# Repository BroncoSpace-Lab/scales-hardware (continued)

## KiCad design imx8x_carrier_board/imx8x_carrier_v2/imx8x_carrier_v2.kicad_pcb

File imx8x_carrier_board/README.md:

# Design Notes

This design for the i.MX 8X SCALES Custom Devlopment Board is mostly based on PhyTec's Development Kit design. For clarity, this version of the SCALES board will be called "SCALES board" and the PhyTec Devlopment Kit board will be called "dev kit."

Version 1 of the SCALES board is for development only. Future versions of the board as we develop for flight will include the power and watchdog system on the same board as the flight computer. The development boards for each of these subsystems will be isolated for testing before combining them into one board for flight.

Most of this design is based on the dev kit schematics and Hardware Manual, available from PhyTec upon request. This link to the [dev kit](https://www.phytec.com/product/phycore-i-mx-8-development-kit/) should supply the necessary supporting documentation used for this design.

## Elements of the SCALES Board

The main elements of the dev kit that are used in the SCALES board are:

- Micro USB UART Debug port
- 2 Ethernet ports
- Micro SD Card Reader

Elements of the dev kit that will be altered significantly for the SCALES board:

- Power input and distribution
- SPI
- UART
- I2C

## Schematic Design

The schematic is organized into heirarchical pages to make the page cleaner and more concise.

The root of the schematic includes the board to board (B2B) connectors that interface the SOM to the SCALES board. The same connectors are used in the dev kit.

This page will be organized to show essential connections between blocks as the schematic progresses.

This version of the SCALES board for development will use DF11 connectors for power input, SPI, UART, and I2C. Later versions of this board for flight will use Gecko connectors. The DF11 is used to reduce lead times for the initial versions of the board.

Important note: all signals from the B2B connectors on the SCALES board begin with "X_". The same naming convention is used in the dev kit.

### Micro USB UART Debug

Replicated as much of the dev kit design as possible. Main changes are:

- MBR0520L is no longer manufactured. using MBR0520LT
- There is a dip switch and a multiplexor that allow for FTDI to be enabled. The dip switch and multiplexor were removed. (they might be brought back later as we continue to develop UART)

### Ethernet

The i.MX 8X SOM has an onboard ethernet transciever for ETH0, but not ETH1. Any carrier board connected to the SOM is required to implement a transciever for ETH1. The design for this transciever and the supporting ethernet female connector plugs were directly pulled from the dev kit schematic, with the only changes being specific part numbers for components and connectors. The functionality is the same.

### Micro SD Card Reader

Everything in the SCALES board is the same as the dev kit except:

- No part # for dip switch selected yet
- Different SD card reader part # used. The one use in the dev kit was not available from JLC PCB.
- Removed Enable_WIFI switch. This signal is pulled low elsewhere for the multiplexor to still work and we do not need WiFi on the SCALES board, so the functionality was removed.

The multiplexor and switches allow you to switch between NAND flash/boot and SD flash/boot. You cannot use SD at the same time as WiFi. Since we will not be using WiFi, this will not be an issue, but the Enable_WIFI signal still needs to be pulled low for the multiplexor to work for switching between SD and NAND.

### Power Input and Distribution

The dev kit used a 12V input. The SOM only requires a 3.3V input at 2A, so we will be using a 3.3V input for the SCALES board.

The dev kit also gets input power from a barrel jack wall plug. The SCALES board (version 1 development) will be getting input from a DF11 2x8 pin connector through a tabletop power supply.

The DF11 power connector used in the SCALES board will also be able to get input power from the SCALES Power Distribution board. Pinouts are still being discussed across boards to maintain consistency.

The power input and distribution system of the imx SCALES board is still in development. Trying to figure out how the voltage rails will translate from the dev kit without the 12V input.

The i.MX 8X SOM generates 3.3V and 1.8V voltage rails, but the dev kit does not use them. Not sure if SCALES should just use the rails or generate new rails.

The dev kit also has a 5V rail, but all the components that use the 5V rail will not be used in SCALES, so it will most likely be omitted. 

### SPI

There are expansion header pins on the last page of the dev kit schematic that allow connection to the SPI pins not in use elsewhere on the board. These signals will be connected to the DF11 for use on the SCALES board.

### UART

The UART on the i.MX 8X dev kit is accessible through header pins, RS232, and the Debug USB. We already covered the Debug USB, so figuring out how to use the signals from the header pins and the RS232 for the DF11 is the next step for the SCALES board. Still in progress.

### I2C

I2C on the dev kit seems pretty straightforward, all that needs to be done is confirm the pinouts for the DF11 with the peripheral board to make sure that everything lines up correctly across both boards for continuity in the design of the system.

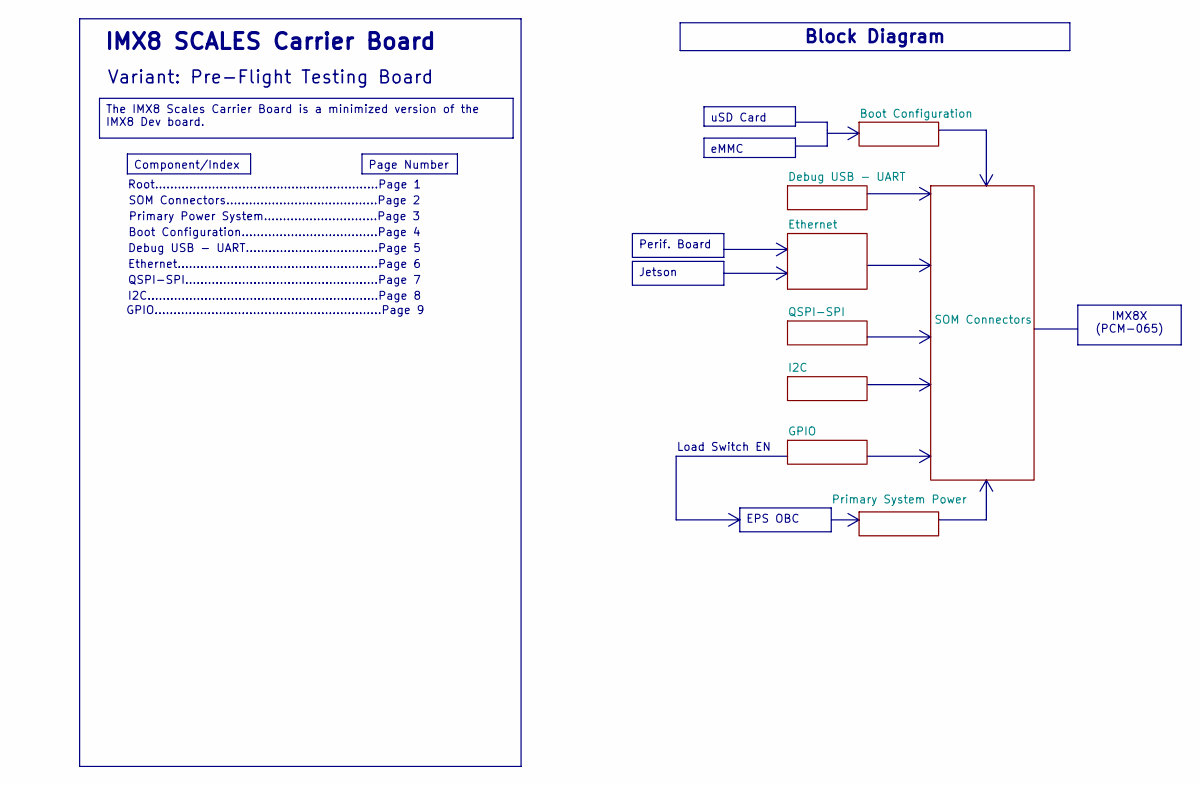
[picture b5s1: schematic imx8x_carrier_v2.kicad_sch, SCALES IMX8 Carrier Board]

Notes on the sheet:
Load Switch EN
Root...........................................................Page 1
SOM Connectors........................................Page 2
Debug USB - UART...................................Page 5
Boot Configuration....................................Page 4
Ethernet.....................................................Page 6
Primary Power System..............................Page 3
QSPI-SPI...................................................Page 7
Variant: Pre-Flight Testing Board
GPIO............................................................Page 9
IMX8 SCALES Carrier Board
I2C.............................................................Page 8
Jetson
Perif. Board
Block Diagram
Component/Index
uSD Card
The IMX8 Scales Carrier Board is a minimized version of the IMX8 Dev board.
IMX8X (PCM-065)
Page Number
EPS OBC
eMMC

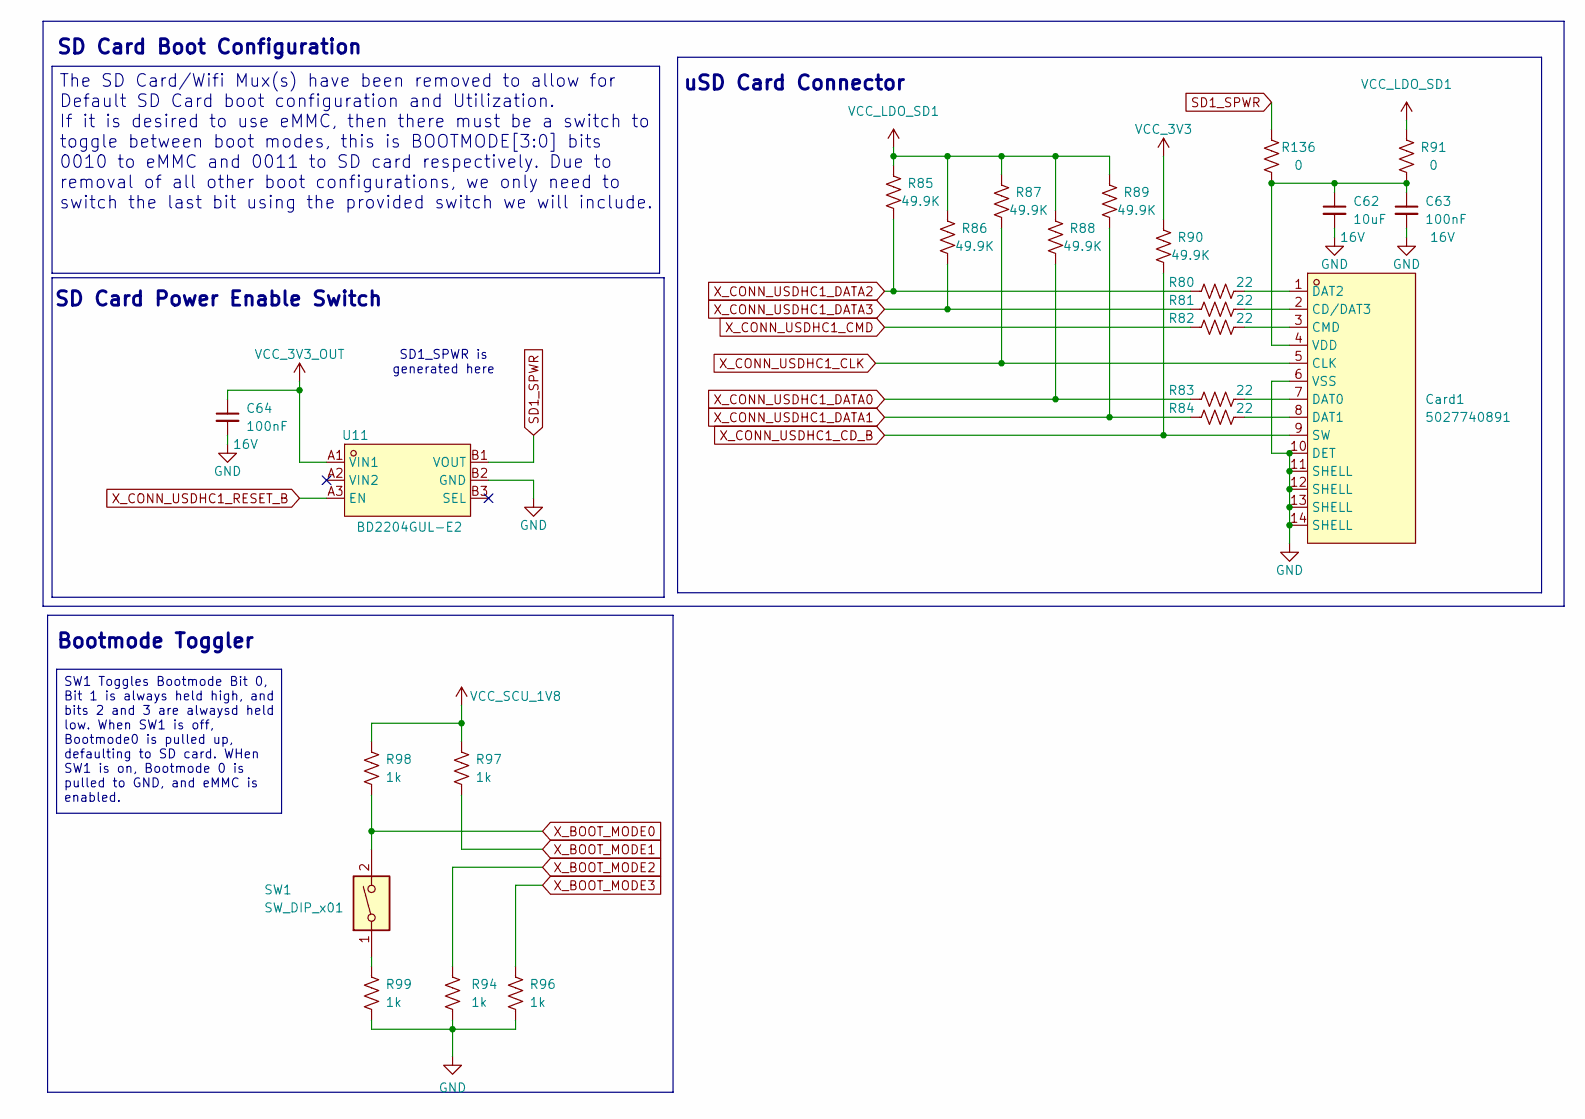
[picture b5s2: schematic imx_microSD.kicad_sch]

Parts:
C62: 10uF; Voltage 16V
C63, C64: 100nF; Voltage 16V
Card1: 5027740891; TF-SMD_5027740891; LCSC Part C330255
R80, R81, R82, R83, R84: 22
R85, R86, R87, R88, R89, R90: 49.9K
R91, R136: 0
R94, R96, R97, R98, R99: 1k
SW1: SW_DIP_x01
U11: BD2204GUL-E2; BGA-6_L1.5-W1.0-P0.50_BD2204GUL-E2; LCSC Part C314699

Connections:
GND: C62.2, C63.2, C64.2, Card1.6 (VSS), Card1.10 (DET), Card1.11 (SHELL), Card1.12 (SHELL), Card1.13 (SHELL), Card1.14 (SHELL), R94.2, R96.2, R99.2, U11.B2 (GND); also elsewhere on the board
unnamed: Card1.2 (CD/DAT3), R81.1
unnamed: Card1.3 (CMD), R82.1
unnamed: Card1.7 (DAT0), R83.1
unnamed: Card1.8 (DAT1), R84.1
unnamed: Card1.1 (DAT2), R80.1
unnamed: C62.1, C63.1, Card1.4 (VDD), R91.2, R136.2
unnamed: R99.1, SW1.1
SD1_SPWR: R136.1, U11.B1 (VOUT)
VCC_3V3: R90.1; also elsewhere on the board
VCC_3V3_OUT: C64.1, U11.A1 (VIN1); also elsewhere on the board
VCC_LDO_SD1: R85.1, R86.1, R87.1, R88.1, R89.1, R91.1; also elsewhere on the board
VCC_SCU_1V8: R97.1, R98.1; also elsewhere on the board
X_BOOT_MODE0: R98.2, SW1.2; also elsewhere on the board
X_BOOT_MODE1: R97.2; also elsewhere on the board
X_BOOT_MODE2: R94.1; also elsewhere on the board
X_BOOT_MODE3: R96.1; also elsewhere on the board
X_CONN_USDHC1_CD_B: Card1.9 (SW), R90.2; also elsewhere on the board
X_CONN_USDHC1_CLK: Card1.5 (CLK), R87.2; also elsewhere on the board
X_CONN_USDHC1_CMD: R82.2; also elsewhere on the board
X_CONN_USDHC1_DATA0: R83.2, R88.2; also elsewhere on the board
X_CONN_USDHC1_DATA1: R84.2, R89.2; also elsewhere on the board
X_CONN_USDHC1_DATA2: R80.2, R85.2; also elsewhere on the board
X_CONN_USDHC1_DATA3: R81.2, R86.2; also elsewhere on the board
X_CONN_USDHC1_RESET_B: U11.A3 (EN); also elsewhere on the board

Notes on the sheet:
SD Card Boot Configuration
SD Card Power Enable Switch
uSD Card Connector
Bootmode Toggler
SD1_SPWR is generated here
The SD Card/Wifi Mux(s) have been removed to allow for Default SD Card boot configuration and Utilization. If it is desired to use eMMC, then there must be a switch to toggle between boot modes, this is BOOTMODE[3:0] bits 0010 to eMMC and 0011 to SD card respectively. Due to removal of all other bo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
SW1 Toggles Bootmode Bit 0, Bit 1 is always held high, and bits 2 and 3 are alwaysd held low. When SW1 is off, Bootmode0 is pulled up, defaulting to SD card. WHen SW1 is on, Bootmode 0 is pulled to GND, and eMMC is enabled.

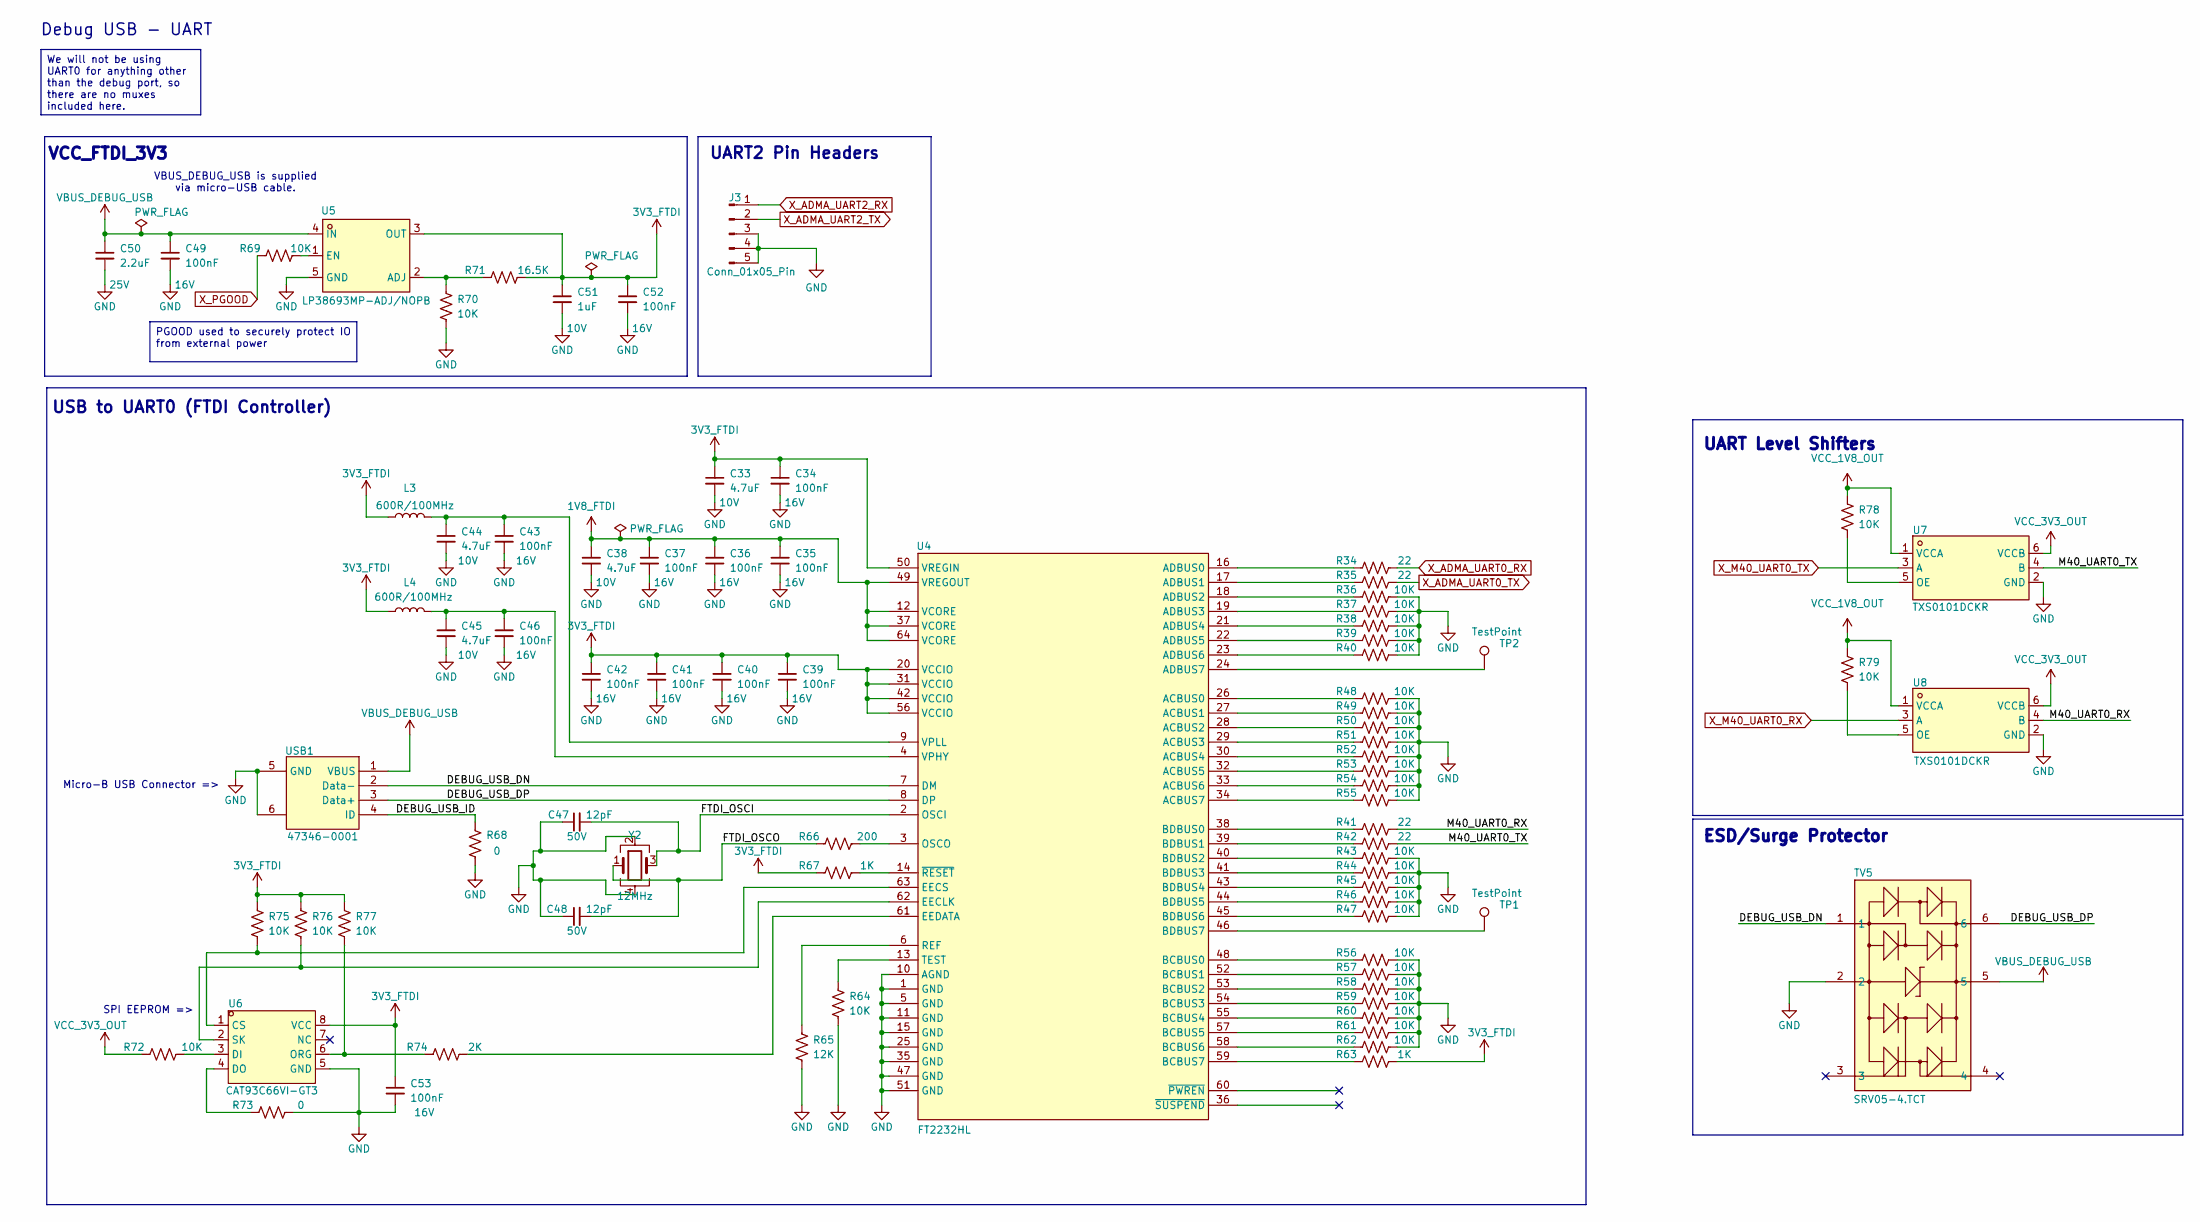
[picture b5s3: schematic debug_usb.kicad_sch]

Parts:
C33, C38, C44, C45: 4.7uF; C_0603_1608Metric; Voltage 10V
C34, C35, C36, C37, C39, C40, C41, C42, C43, C46, C49, C52, C53: 100nF; C_0603_1608Metric; Voltage 16V
C47, C48: 12pF; C_0603_1608Metric; Voltage 50V
C50: 2.2uF; C_0603_1608Metric; Voltage 25V
C51: 1uF; C_0603_1608Metric; Voltage 10V
J3: Conn_01x05_Pin; PinHeader_1x05_P2.54mm_Vertical
L3, L4: 600R/100MHz; L0805
R34, R35, R41, R42: 22; R_0402_1005Metric
R36, R37, R38, R39, R40, R43, R44, R45, R46, R47, R48, R49, R50, R51, R52, R53, R54, R55, R56, R57, R58, R59, R60, R61, R62, R64, R69, R70, R72, R75, R76, R77, R78, R79: 10K; R_0402_1005Metric
R63, R67: 1K; R_0402_1005Metric
R65: 12K; R_0402_1005Metric
R66: 200; R_0402_1005Metric
R68, R73: 0; R_0402_1005Metric
R71: 16.5K; R_0402_1005Metric
R74: 2K; R_0402_1005Metric
TP1, TP2: TestPoint; TestPoint_THTPad_1.0x1.0mm_Drill0.5mm
TV5: SRV05-4.TCT; SOT-23-6_L2.9-W1.6-P0.95-LS2.8-BR; LCSC Part C13612
U4: FT2232HL; LQFP-64_L10.0-W10.0-P0.50-LS12.0-TL; LCSC Part C27882
U5: LP38693MP-ADJ/NOPB; SOT-223-5_L6.5-W3.5-P1.50-LS7.0-BL; LCSC Part C181420
U6: CAT93C66VI-GT3; SOIC-8_L4.9-W3.9-P1.27-LS6.0-BL; LCSC Part C890471
U7, U8: TXS0101DCKR; SC-70-6_L2.0-W1.3-P0.65-LS2.1-BR; LCSC Part C132031
USB1: 47346-0001; MICRO-USB-SMD_47346-0001; LCSC Part C132560
Y2: 12MHz; CRYSTAL-SMD_4P-L3.2-W2.5-BL; LCSC Part C9002

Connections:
1V8_FTDI: C35.1, C36.1, C37.1, C38.1, U4.12 (VCORE), U4.37 (VCORE), U4.49 (VREGOUT), U4.64 (VCORE)
3V3_FTDI: C33.1, C34.1, C39.1, C40.1, C41.1, C42.1, C51.1, C52.1, C53.1, L3.1, L4.1, R63.1, R67.2, R71.1, R75.1, R76.1, R77.1, U4.20 (VCCIO), U4.31 (VCCIO), U4.42 (VCCIO), U4.50 (VREGIN), U4.56 (VCCIO), U5.3 (OUT), U6.8 (VCC)
/Debug USB - UART/DEBUG_USB_DN: TV5.1, U4.7 (DM), USB1.2 (Data-)
/Debug USB - UART/DEBUG_USB_DP: TV5.6, U4.8 (DP), USB1.3 (Data+)
/Debug USB - UART/DEBUG_USB_ID: R68.1, USB1.4 (ID)
/Debug USB - UART/FTDI_OSCI: C47.2, U4.2 (OSCI), Y2.3
/Debug USB - UART/FTDI_OSCO: C48.2, R66.2, Y2.1
/Debug USB - UART/M40_UART0_RX: R41.1, U8.4 (B)
/Debug USB - UART/M40_UART0_TX: R42.1, U7.4 (B)
GND: C33.2, C34.2, C35.2, C36.2, C37.2, C38.2, C39.2, C40.2, C41.2, C42.2, C43.2, C44.2, C45.2, C46.2, C47.1, C48.1, C49.2, C50.2, C51.2, C52.2, C53.2, J3.3, J3.4, J3.5, R36.1, R37.1, R38.1, R39.1, R40.1, R43.1, R44.1, R45.1, R46.1, R47.1, R48.1, R49.1, R50.1, R51.1, R52.1, R53.1, R54.1, R55.1, R56.1, R57.1, R58.1, R59.1, R60.1, R61.1, R62.1, R64.2, R65.2, R68.2, R70.2, R73.1, TV5.2, U4.1 (GND), U4.5 (GND), U4.10 (AGND), U4.11 (GND), U4.15 (GND), U4.25 (GND), U4.35 (GND), U4.47 (GND), U4.51 (GND), U5.5 (GND), U6.5 (GND), U7.2 (GND), U8.2 (GND), USB1.5 (GND), USB1.6, Y2.2, Y2.4; also elsewhere on the board
unnamed: R48.2, U4.26 (ACBUS0)
unnamed: R49.2, U4.27 (ACBUS1)
unnamed: R50.2, U4.28 (ACBUS2)
unnamed: R51.2, U4.29 (ACBUS3)
unnamed: R52.2, U4.30 (ACBUS4)
unnamed: R53.2, U4.32 (ACBUS5)
unnamed: R54.2, U4.33 (ACBUS6)
unnamed: R55.2, U4.34 (ACBUS7)
unnamed: R34.2, U4.16 (ADBUS0)
unnamed: R35.2, U4.17 (ADBUS1)
unnamed: R36.2, U4.18 (ADBUS2)
unnamed: R37.2, U4.19 (ADBUS3)
unnamed: R38.2, U4.21 (ADBUS4)
unnamed: R39.2, U4.22 (ADBUS5)
unnamed: R40.2, U4.23 (ADBUS6)
unnamed: TP2.1, U4.24 (ADBUS7)
unnamed: R56.2, U4.48 (BCBUS0)
unnamed: R57.2, U4.52 (BCBUS1)
unnamed: R58.2, U4.53 (BCBUS2)
unnamed: R59.2, U4.54 (BCBUS3)
unnamed: R60.2, U4.55 (BCBUS4)
unnamed: R61.2, U4.57 (BCBUS5)
unnamed: R62.2, U4.58 (BCBUS6)
unnamed: R63.2, U4.59 (BCBUS7)
unnamed: R41.2, U4.38 (BDBUS0)
unnamed: R42.2, U4.39 (BDBUS1)
unnamed: R43.2, U4.40 (BDBUS2)
unnamed: R44.2, U4.41 (BDBUS3)
unnamed: R45.2, U4.43 (BDBUS4)
unnamed: R46.2, U4.44 (BDBUS5)
unnamed: R47.2, U4.45 (BDBUS6)
unnamed: TP1.1, U4.46 (BDBUS7)
unnamed: R76.2, U4.62 (EECLK), U6.2 (SK)
unnamed: R75.2, U4.63 (EECS), U6.1 (CS)
unnamed: R74.1, U4.61 (EEDATA)
unnamed: R66.1, U4.3 (OSCO)
unnamed: R65.1, U4.6 (REF)
unnamed: R64.1, U4.13 (TEST)
unnamed: C45.1, C46.1, L4.2, U4.4 (VPHY)
unnamed: C43.1, C44.1, L3.2, U4.9 (VPLL)
unnamed: R67.1, U4.14 (~RESET)
unnamed: R70.1, R71.2, U5.2 (ADJ)
unnamed: R69.1, U5.1 (EN)
unnamed: R72.1, U6.3 (DI)
unnamed: R73.2, U6.4 (DO)
unnamed: R74.2, R77.2, U6.6 (ORG)
unnamed: R78.2, U7.5 (OE)
unnamed: R79.2, U8.5 (OE)
VBUS_DEBUG_USB: C49.1, C50.1, TV5.5, U5.4 (IN), USB1.1 (VBUS)
VCC_1V8_OUT: R78.1, R79.1, U7.1 (VCCA), U8.1 (VCCA); also elsewhere on the board
VCC_3V3_OUT: R72.2, U7.6 (VCCB), U8.6 (VCCB); also elsewhere on the board
X_ADMA_UART0_RX: R34.1; also elsewhere on the board
X_ADMA_UART0_TX: R35.1; also elsewhere on the board
X_ADMA_UART2_RX: J3.1; also elsewhere on the board
X_ADMA_UART2_TX: J3.2; also elsewhere on the board
X_M40_UART0_RX: U8.3 (A); also elsewhere on the board
X_M40_UART0_TX: U7.3 (A); also elsewhere on the board
X_PGOOD: R69.2; also elsewhere on the board

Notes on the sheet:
ESD/Surge Protector
UART Level Shifters
Micro-B USB Connector =>
UART2 Pin Headers
VCC_FTDI_3V3
VBUS_DEBUG_USB is supplied via micro-USB cable.
SPI EEPROM =>
Debug USB - UART
USB to UART0 (FTDI Controller)
PGOOD used to securely protect IO from external power
We will not be using UART0 for anything other than the debug port, so there are no muxes included here.

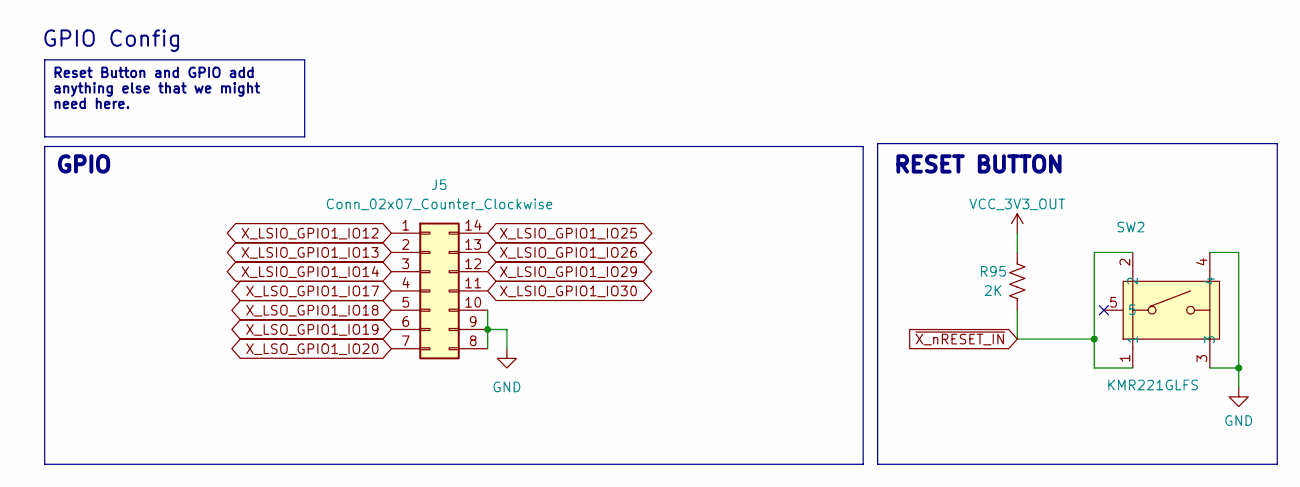
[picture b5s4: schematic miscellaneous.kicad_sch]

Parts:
J5: Conn_02x07_Counter_Clockwise; PinHeader_2x07_P2.54mm_Vertical
R95: 2K; R_0402_1005Metric
SW2: KMR221GLFS; KEY-SMD_KMR2XXGXXX; LCSC Part C72443

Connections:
GND: J5.8, J5.9, J5.10, SW2.3, SW2.4; also elsewhere on the board
VCC_3V3_OUT: R95.2; also elsewhere on the board
X_LSIO_GPIO1_IO12: J5.1; also elsewhere on the board
X_LSIO_GPIO1_IO13: J5.2; also elsewhere on the board
X_LSIO_GPIO1_IO14: J5.3; also elsewhere on the board
X_LSIO_GPIO1_IO25: J5.14; also elsewhere on the board
X_LSIO_GPIO1_IO26: J5.13; also elsewhere on the board
X_LSIO_GPIO1_IO29: J5.12; also elsewhere on the board
X_LSIO_GPIO1_IO30: J5.11; also elsewhere on the board
X_LSO_GPIO1_IO17: J5.4; also elsewhere on the board
X_LSO_GPIO1_IO18: J5.5; also elsewhere on the board
X_LSO_GPIO1_IO19: J5.6; also elsewhere on the board
X_LSO_GPIO1_IO20: J5.7; also elsewhere on the board
~X_nRESET_IN: R95.1, SW2.1, SW2.2; also elsewhere on the board

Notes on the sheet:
GPIO Config
RESET BUTTON
GPIO
Reset Button and GPIO add anything else that we might need here.

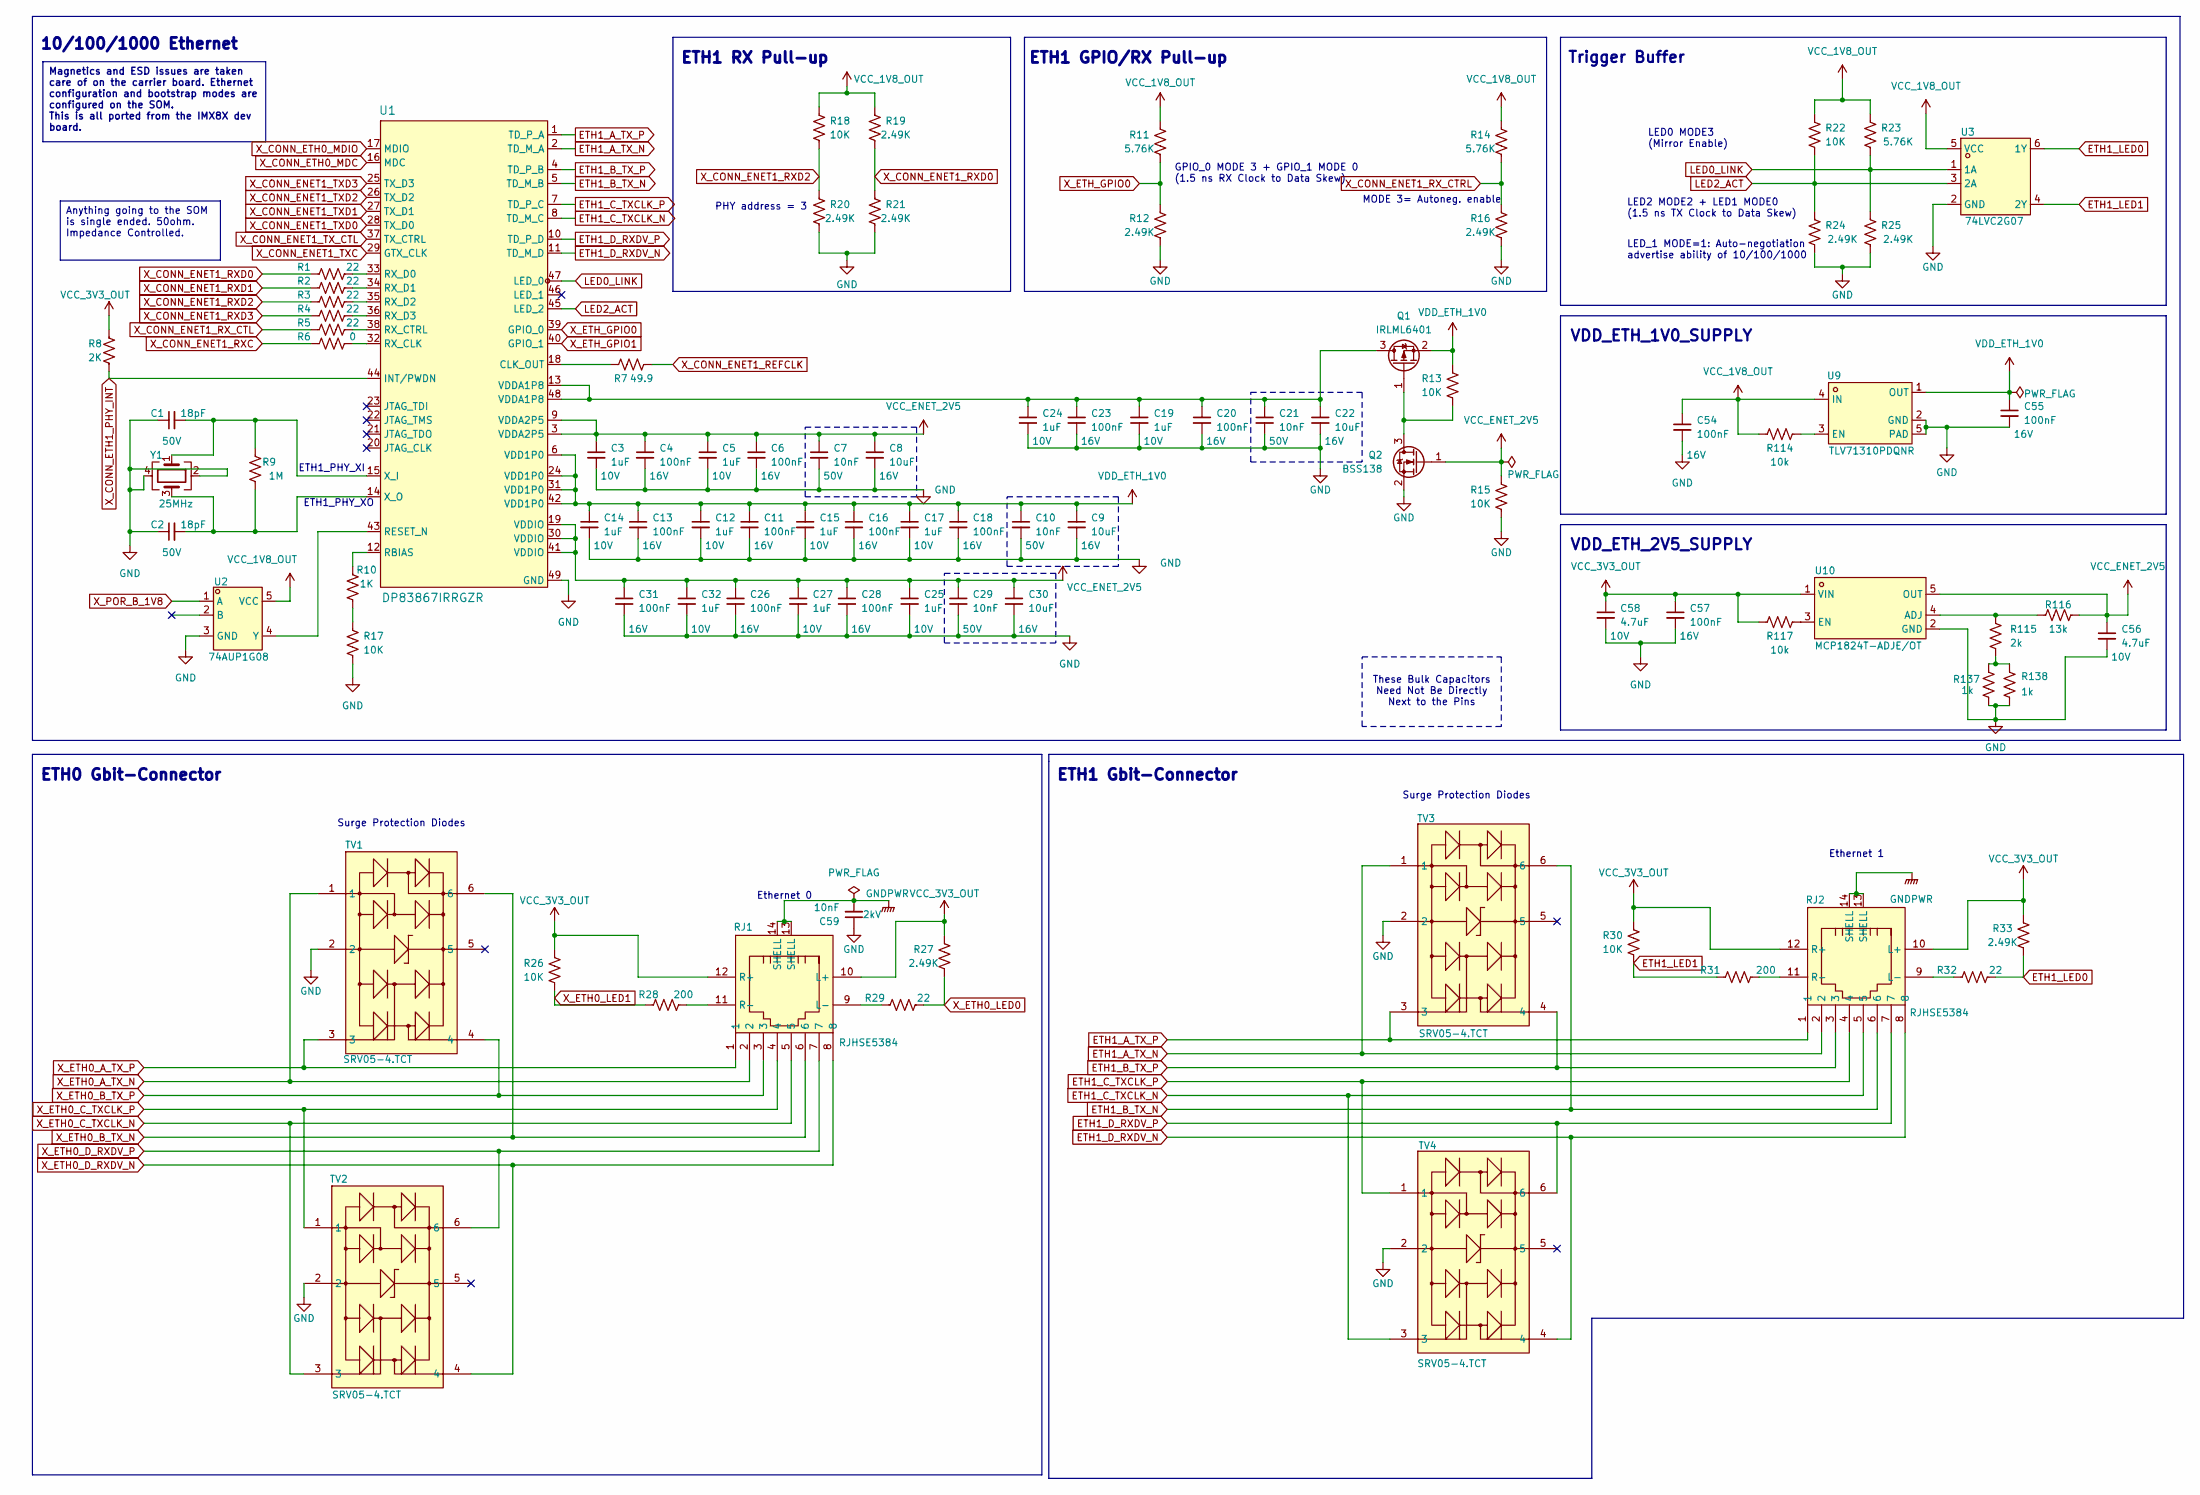
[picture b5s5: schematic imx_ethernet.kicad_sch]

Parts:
C1, C2: 18pF; C_0603_1608Metric; Voltage 50V
C3, C5, C12, C14, C15, C17, C19, C24, C25, C27, C32: 1uF; C_0603_1608Metric; Voltage 10V
C4, C6, C11, C13, C16, C18, C20, C23, C26, C28, C31, C54, C55, C57: 100nF; C_0603_1608Metric; Voltage 16V
C7, C10, C21, C29: 10nF; C_0603_1608Metric; Voltage 50V
C8, C9, C22, C30: 10uF; C_0603_1608Metric; Voltage 16V
C56, C58: 4.7uF; C_0603_1608Metric; Voltage 10V
C59: 10nF; C_0603_1608Metric; Voltage 2kV
Q1: IRLML6401; SOT-23
Q2: BSS138; SOT-23
R1, R2, R3, R4, R5, R29, R32: 22; R_0402_1005Metric
R6: 0; R_0402_1005Metric
R7: 49.9; R_0402_1005Metric
R8: 2K; R_0402_1005Metric
R9: 1M; R_0402_1005Metric
R10: 1K; R_0402_1005Metric
R11, R14, R23: 5.76K; R_0402_1005Metric
R12, R16, R19, R20, R21, R24, R25, R27, R33: 2.49K; R_0402_1005Metric
R13, R15, R17, R18, R22, R26, R30: 10K; R_0402_1005Metric
R28, R31: 200; R_0402_1005Metric
R114, R117: 10k; R_0402_1005Metric
R115: 2k; R_0402_1005Metric
R116: 13k; R_0402_1005Metric
R137, R138: 1k; R_0402_1005Metric
RJ1, RJ2: RJHSE5384; RJ45-TH_RJHSE5384; LCSC Part C464587
TV1, TV2, TV3, TV4: SRV05-4.TCT; SOT-23-6_L2.9-W1.6-P0.95-LS2.8-BR; LCSC Part C13612
U1: DP83867IRRGZR; VQFN-48_L7.0-W7.0-P0.50-BL-EP4.1; LCSC Part C544766
U2: 74AUP1G08; SOT-23-5_L3.0-W1.7-P0.95-LS2.8-BR; LCSC Part C139409
U3: 74LVC2G07; SOT-363_L2.1-W1.3-P0.65-LS2.2-BL; LCSC Part C19829574
U9: TLV71310PDQNR; X2SON-4_L1.0-W1.0-P0.65-TL-EP; LCSC Part C2872754
U10: MCP1824T-ADJE/OT; SOT-23-5_L3.0-W1.7-P0.95-LS2.8-BL; LCSC Part C145717
Y1: 25MHz; CRYSTAL-SMD_4P-L3.2-W2.5-BL-2; LCSC C13740

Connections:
ETH1_A_TX_N: RJ2.2, TV3.1, U1.2 (TD_M_A)
ETH1_A_TX_P: RJ2.1, TV3.3, U1.1 (TD_P_A)
ETH1_B_TX_N: RJ2.6, TV3.6, U1.5 (TD_M_B)
ETH1_B_TX_P: RJ2.3, TV3.4, U1.4 (TD_P_B)
ETH1_C_TXCLK_N: RJ2.5, TV4.3, U1.8 (TD_M_C)
ETH1_C_TXCLK_P: RJ2.4, TV4.1, U1.7 (TD_P_C)
ETH1_D_RXDV_N: RJ2.8, TV4.4, U1.11 (TD_M_D)
ETH1_D_RXDV_P: RJ2.7, TV4.6, U1.10 (TD_P_D)
ETH1_LED0: R32.1, R33.2, U3.6 (1Y)
ETH1_LED1: R30.2, R31.2, U3.4 (2Y)
GND: C1.1, C2.1, C3.2, C4.2, C5.2, C6.2, C7.2, C8.2, C9.2, C10.2, C11.2, C12.2, C13.2, C14.2, C15.2, C16.2, C17.2, C18.2, C19.2, C20.2, C21.2, C22.2, C23.2, C24.2, C25.2, C26.2, C27.2, C28.2, C29.2, C30.2, C31.2, C32.2, C54.2, C55.2, C56.2, C57.2, C58.2, C59.1, Q2.2 (S), R12.2, R15.2, R16.2, R17.2, R20.2, R21.2, R24.2, R25.2, R137.1, R138.1, TV1.2, TV2.2, TV3.2, TV4.2, U1.49 (GND), U2.3 (GND), U3.2 (GND), U9.2 (GND), U9.5 (PAD), U10.2 (GND), Y1.2, Y1.4; also elsewhere on the board
GNDPWR: C59.2, RJ1.13 (SHELL), RJ1.14 (SHELL), RJ2.13 (SHELL), RJ2.14 (SHELL)
LED0_LINK: R23.2, R25.1, U1.47 (LED_0), U3.1 (1A)
LED2_ACT: R22.2, R24.1, U1.45 (LED_2), U3.3 (2A)
unnamed: C19.1, C20.1, C21.1, C22.1, C23.1, C24.1, Q1.3 (D), U1.13 (VDDA1P8), U1.48 (VDDA1P8)
unnamed: Q1.1 (G), Q2.3 (D), R13.2
unnamed: R10.2, R17.1
unnamed: R115.1, R137.2, R138.2
unnamed: R29.2, RJ1.9 (L-)
unnamed: R28.1, RJ1.11 (R-)
unnamed: R32.2, RJ2.9 (L-)
unnamed: R31.1, RJ2.11 (R-)
unnamed: R7.2, U1.18 (CLK_OUT)
unnamed: R10.1, U1.12 (RBIAS)
unnamed: U1.43 (RESET_N), U2.4 (Y)
unnamed: R6.1, U1.32 (RX_CLK)
unnamed: R5.1, U1.38 (RX_CTRL)
unnamed: R1.1, U1.33 (RX_D0)
unnamed: R2.1, U1.34 (RX_D1)
unnamed: R3.1, U1.35 (RX_D2)
unnamed: R4.1, U1.36 (RX_D3)
unnamed: C1.2, R9.1, U1.15 (X_I), Y1.1
unnamed: C2.2, R9.2, U1.14 (X_O), Y1.3
unnamed: R114.2, U9.3 (EN)
unnamed: R115.2, R116.2, U10.4 (ADJ)
unnamed: R117.2, U10.3 (EN)
VCC_1V8_OUT: C54.1, R11.1, R14.1, R18.1, R19.1, R22.1, R23.1, R114.1, U2.5 (VCC), U3.5 (VCC), U9.4 (IN); also elsewhere on the board
VCC_3V3_OUT: C57.1, C58.1, R8.2, R26.1, R27.1, R30.1, R33.1, R117.1, RJ1.10 (L+), RJ1.12 (R+), RJ2.10 (L+), RJ2.12 (R+), U10.1 (VIN); also elsewhere on the board
VCC_ENET_2V5: C3.1, C4.1, C5.1, C6.1, C7.1, C8.1, C25.1, C26.1, C27.1, C28.1, C29.1, C30.1, C31.1, C32.1, C56.1, Q2.1 (G), R15.1, R116.1, U1.3 (VDDA2P5), U1.9 (VDDA2P5), U1.19 (VDDIO), U1.30 (VDDIO), U1.41 (VDDIO), U10.5 (OUT)
VDD_ETH_1V0: C9.1, C10.1, C11.1, C12.1, C13.1, C14.1, C15.1, C16.1, C17.1, C18.1, C55.1, Q1.2 (S), R13.1, U1.6 (VDD1P0), U1.24 (VDD1P0), U1.31 (VDD1P0), U1.42 (VDD1P0), U9.1 (OUT)
X_CONN_ENET1_REFCLK: R7.1; also elsewhere on the board
X_CONN_ENET1_RXC: R6.2; also elsewhere on the board
X_CONN_ENET1_RXD0: R1.2, R19.2, R21.1; also elsewhere on the board
X_CONN_ENET1_RXD1: R2.2; also elsewhere on the board
X_CONN_ENET1_RXD2: R3.2, R18.2, R20.1; also elsewhere on the board
X_CONN_ENET1_RXD3: R4.2; also elsewhere on the board
X_CONN_ENET1_RX_CTL: R5.2; also elsewhere on the board
X_CONN_ENET1_RX_CTRL: R14.2, R16.1
X_CONN_ENET1_TXC: U1.29 (GTX_CLK); also elsewhere on the board
X_CONN_ENET1_TXD0: U1.28 (TX_D0); also elsewhere on the board
X_CONN_ENET1_TXD1: U1.27 (TX_D1); also elsewhere on the board
X_CONN_ENET1_TXD2: U1.26 (TX_D2); also elsewhere on the board
X_CONN_ENET1_TXD3: U1.25 (TX_D3); also elsewhere on the board
X_CONN_ENET1_TX_CTL: U1.37 (TX_CTRL); also elsewhere on the board
X_CONN_ETH0_MDC: U1.16 (MDC); also elsewhere on the board
X_CONN_ETH0_MDIO: U1.17 (MDIO); also elsewhere on the board
X_CONN_ETH1_PHY_INT: R8.1, U1.44 (INT/PWDN)
X_ETH0_A_TX_N: RJ1.2, TV1.1; also elsewhere on the board
X_ETH0_A_TX_P: RJ1.1, TV1.3; also elsewhere on the board
X_ETH0_B_TX_N: RJ1.6, TV1.6; also elsewhere on the board
X_ETH0_B_TX_P: RJ1.3, TV1.4; also elsewhere on the board
X_ETH0_C_TXCLK_N: RJ1.5, TV2.3; also elsewhere on the board
X_ETH0_C_TXCLK_P: RJ1.4, TV2.1; also elsewhere on the board
X_ETH0_D_RXDV_N: RJ1.8, TV2.4; also elsewhere on the board
X_ETH0_D_RXDV_P: RJ1.7, TV2.6; also elsewhere on the board
X_ETH0_LED0: R27.2, R29.1; also elsewhere on the board
X_ETH0_LED1: R26.2, R28.2; also elsewhere on the board
X_ETH_GPIO0: R11.2, R12.1, U1.39 (GPIO_0); also elsewhere on the board
X_ETH_GPIO1: U1.40 (GPIO_1); also elsewhere on the board
X_POR_B_1V8: U2.1 (A); also elsewhere on the board

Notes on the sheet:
Trigger Buffer
Ethernet 0
ETH0 Gbit-Connector
These Bulk Capacitors Need Not Be Directly Next to the Pins
VDD_ETH_2V5_SUPPLY
Surge Protection Diodes
ETH1 Gbit-Connector
Ethernet 1
ETH1 GPIO/RX Pull-up
LED2 MODE2 + LED1 MODE0 (1.5 ns TX Clock to Data Skew)
ETH1_PHY_XO
GPIO_0 MODE 3 + GPIO_1 MODE 0 (1.5 ns RX Clock to Data Skew)
LED0 MODE3 (Mirror Enable)
ETH1 RX Pull-up
10/100/1000 Ethernet
ETH1_PHY_XI
PHY address = 3
MODE 3= Autoneg. enable
VDD_ETH_1V0_SUPPLY
LED_1 MODE=1: Auto-negotiation advertise ability of 10/100/1000
Magnetics and ESD issues are taken care of on the carrier board. Ethernet configuration and bootstrap modes are configured on the SOM. This is all ported from the IMX8X dev board.
Anything going to the SOM is single ended. 50ohm. Impedance Controlled.

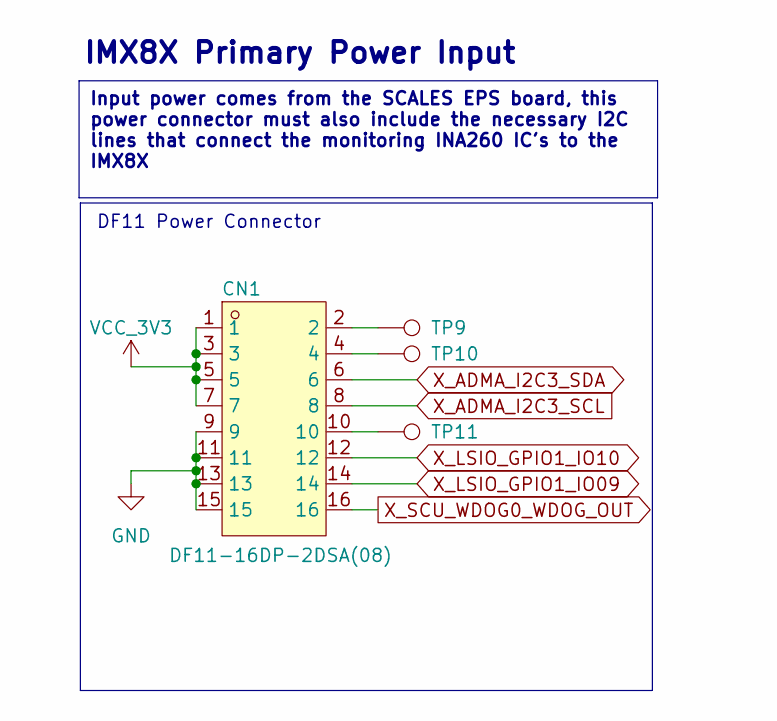
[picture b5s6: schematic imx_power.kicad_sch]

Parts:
CN1: DF11-16DP-2DSA(08); CONN-TH_DF11-16DP-2DSA-08; LCSC Part C530981
TP9, TP10, TP11: TestPoint; TestPoint_THTPad_1.0x1.0mm_Drill0.5mm

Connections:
GND: CN1.9, CN1.11, CN1.13, CN1.15; also elsewhere on the board
unnamed: CN1.2, TP9.1
unnamed: CN1.4, TP10.1
unnamed: CN1.10, TP11.1
VCC_3V3: CN1.1, CN1.3, CN1.5, CN1.7; also elsewhere on the board
X_ADMA_I2C3_SCL: CN1.8; also elsewhere on the board
X_ADMA_I2C3_SDA: CN1.6; also elsewhere on the board
X_LSIO_GPIO1_IO09: CN1.14; also elsewhere on the board
X_LSIO_GPIO1_IO10: CN1.12; also elsewhere on the board
X_SCU_WDOG0_WDOG_OUT: CN1.16; also elsewhere on the board

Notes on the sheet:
DF11 Power Connector
IMX8X Primary Power Input
Input power comes from the SCALES EPS board, this power connector must also include the necessary I2C lines that connect the monitoring INA260 IC's to the IMX8X

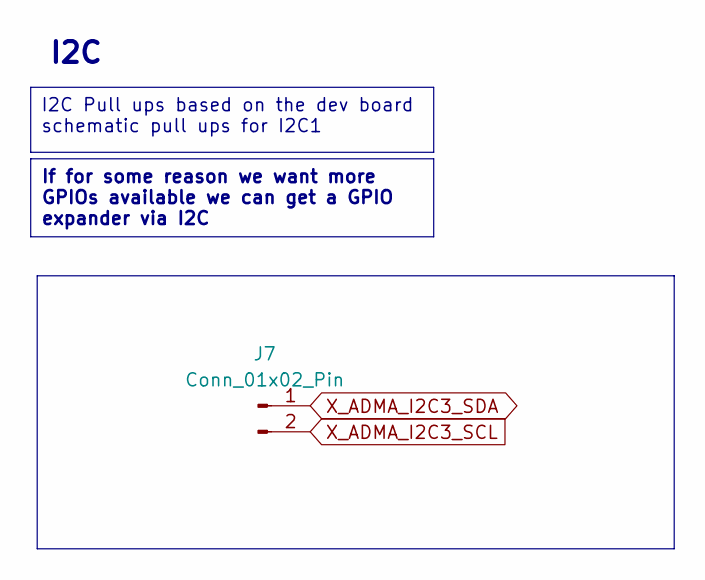
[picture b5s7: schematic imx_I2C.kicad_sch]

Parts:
J7: Conn_01x02_Pin; PinHeader_1x02_P2.54mm_Vertical

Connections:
X_ADMA_I2C3_SCL: J7.2; also elsewhere on the board
X_ADMA_I2C3_SDA: J7.1; also elsewhere on the board

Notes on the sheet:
I2C
I2C Pull ups based on the dev board schematic pull ups for I2C1
If for some reason we want more GPIOs available we can get a GPIO expander via I2C
